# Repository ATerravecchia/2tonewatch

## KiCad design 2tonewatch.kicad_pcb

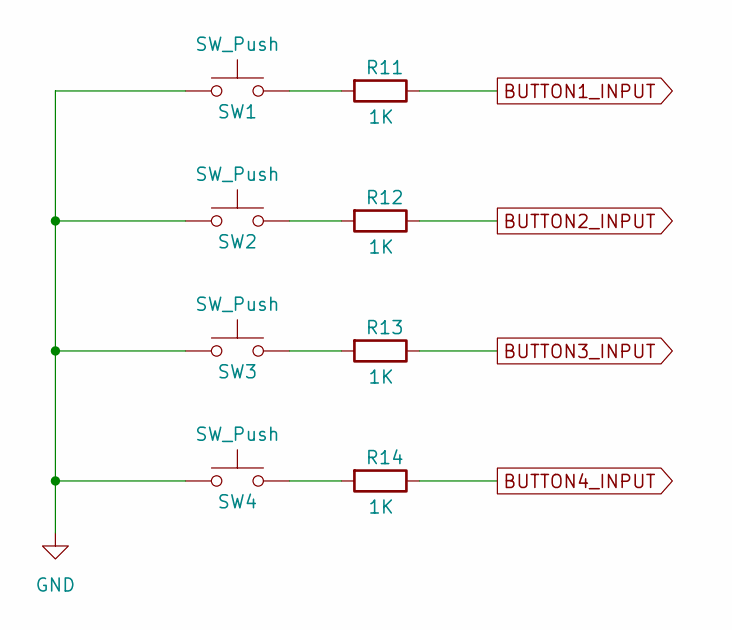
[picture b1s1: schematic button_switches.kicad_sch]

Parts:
R11, R12, R13, R14: 1K; R_0402_1005Metric
SW1, SW2, SW3, SW4: SW_Push; SW_SPST_B3U-3000P; MPN B3U-3000P

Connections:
BUTTON1_INPUT: R11.1; also elsewhere on the board
BUTTON2_INPUT: R12.1; also elsewhere on the board
BUTTON3_INPUT: R13.1; also elsewhere on the board
BUTTON4_INPUT: R14.1; also elsewhere on the board
GND: SW1.1, SW2.1, SW3.1, SW4.1; also elsewhere on the board
unnamed: R11.2, SW1.2
unnamed: R12.2, SW2.2
unnamed: R13.2, SW3.2
unnamed: R14.2, SW4.2

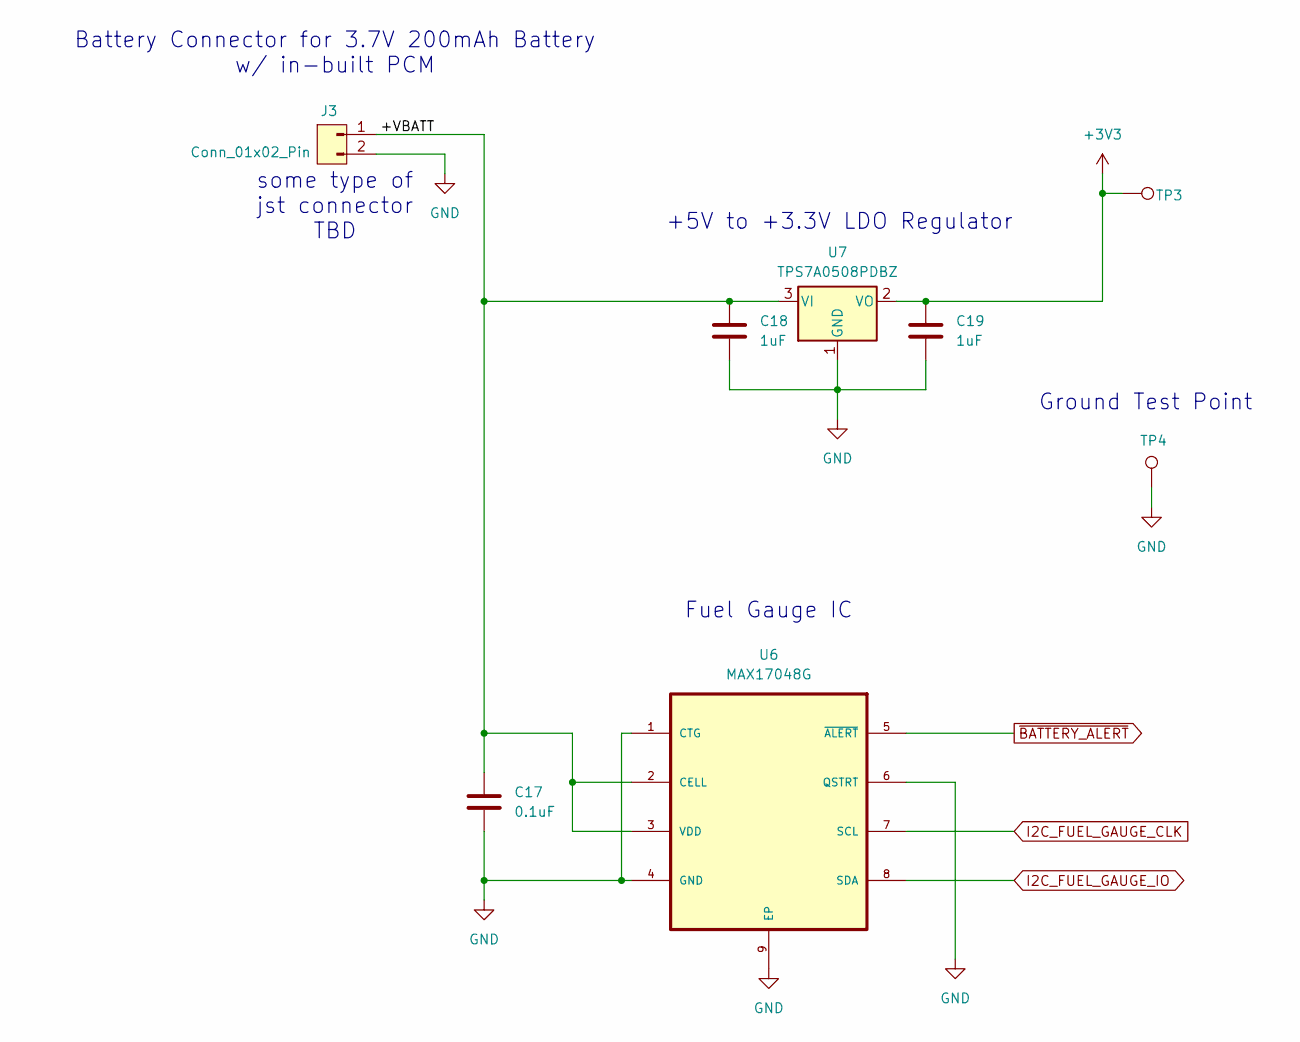
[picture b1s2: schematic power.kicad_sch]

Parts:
C17: 0.1uF; C_0402_1005Metric
C18, C19: 1uF; C_0402_1005Metric
J3: Conn_01x02_Pin; JST_PH_B2B-PH-K_1x02_P2.00mm_Vertical
TP3, TP4: TestPoint_Pad_D1.0mm
U6: MAX17048G; TDFN-8-1EP_2x2mm_P0.5mm_EP0.8x1.2mm
U7: TPS7A0508PDBZ; SOT-23

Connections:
+3V3: C19.1, TP3.1, U7.2 (VO); also elsewhere on the board
/Power/+VBATT: C17.1, C18.1, J3.1, U6.2 (CELL), U6.3 (VDD), U7.3 (VI)
GND: C17.2, C18.2, C19.2, J3.2, TP4.1, U6.1 (CTG), U6.4 (GND), U6.6 (QSTRT), U6.9 (EP), U7.1 (GND); also elsewhere on the board
I2C_FUEL_GAUGE_CLK: U6.7 (SCL); also elsewhere on the board
I2C_FUEL_GAUGE_IO: U6.8 (SDA); also elsewhere on the board
~BATTERY_ALERT: U6.5 (~ALERT); also elsewhere on the board

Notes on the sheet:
Fuel Gauge IC
Ground Test Point
Battery Connector for 3.7V 200mAh Battery w/ in-built PCM
some type of jst connector TBD
+5V to +3.3V LDO Regulator

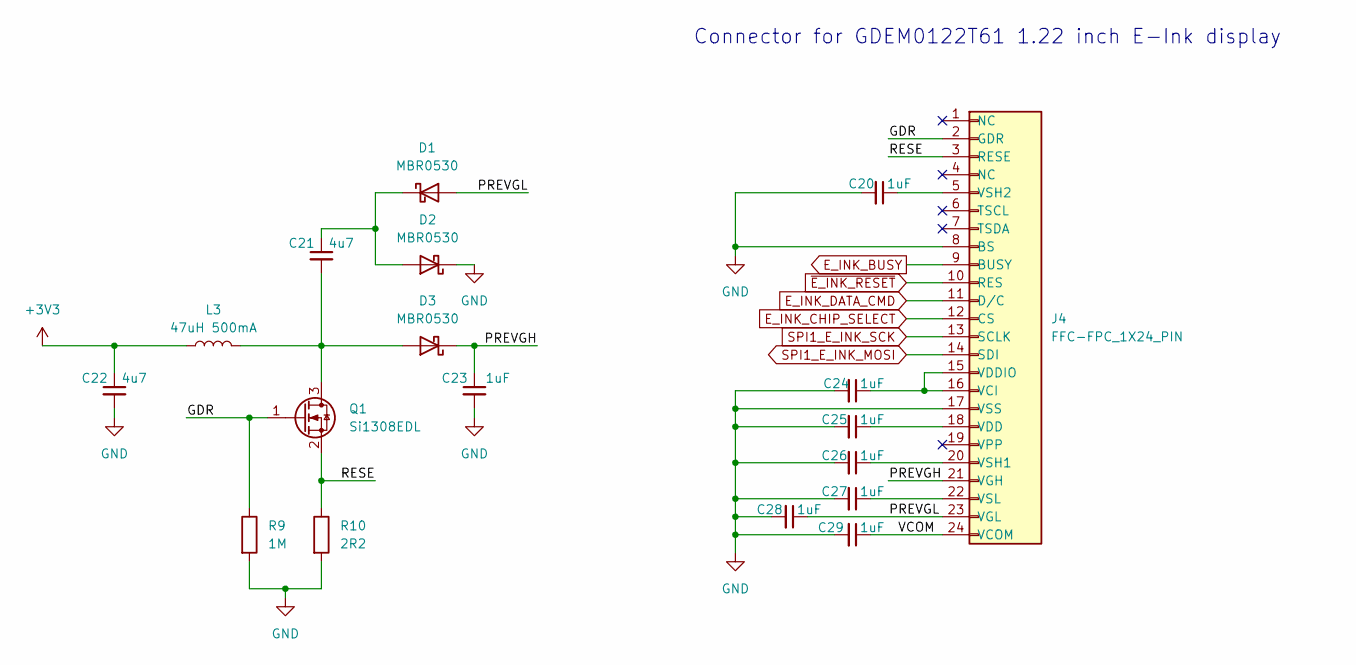
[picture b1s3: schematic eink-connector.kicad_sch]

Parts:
C20, C23, C24, C25, C26, C27, C28, C29: 1uF; C_0603_1608Metric
C21, C22: 4u7; C_0603_1608Metric
D1, D2, D3: MBR0530; D_SOD-123
J4: FFC-FPC_1X24_PIN; Amphenol_F32Q-1A7x1-11024_1x24-1MP_P0.5mm_Horizontal
L3: 47uH 500mA; L_1210_3225Metric; MPN ADL3225V-470MT-TL000
Q1: Si1308EDL; SOT-323_SC-70
R9: 1M; R_0603_1608Metric
R10: 2R2; R_0603_1608Metric

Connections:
+3V3: C22.1, L3.1; also elsewhere on the board
/eink-connector/GDR: J4.2 (GDR), Q1.1 (G), R9.1
/eink-connector/PREVGH: C23.1, D3.1 (K), J4.21 (VGH)
/eink-connector/PREVGL: C28.1, D1.2 (A), J4.23 (VGL)
/eink-connector/RESE: J4.3 (RESE), Q1.2 (S), R10.1
/eink-connector/VCOM: C29.1, J4.24 (VCOM)
E_INK_BUSY: J4.9 (BUSY); also elsewhere on the board
E_INK_CHIP_SELECT: J4.12 (CS); also elsewhere on the board
E_INK_DATA_CMD: J4.11 (D/C); also elsewhere on the board
GND: C20.2, C22.2, C23.2, C24.2, C25.2, C26.2, C27.2, C28.2, C29.2, D2.1 (K), J4.8 (BS), J4.17 (VSS), R9.2, R10.2; also elsewhere on the board
unnamed: C21.1, D1.1 (K), D2.2 (A)
unnamed: C21.2, D3.2 (A), L3.2, Q1.3 (D)
unnamed: C24.1, J4.15 (VDDIO), J4.16 (VCI)
unnamed: C25.1, J4.18 (VDD)
unnamed: C26.1, J4.20 (VSH1)
unnamed: C20.1, J4.5 (VSH2)
unnamed: C27.1, J4.22 (VSL)
SPI1_E_INK_MOSI: J4.14 (SDI); also elsewhere on the board
SPI1_E_INK_SCK: J4.13 (SCLK); also elsewhere on the board
~E_INK_RESET: J4.10 (RES); also elsewhere on the board

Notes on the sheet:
Connector for GDEM0122T61 1.22 inch E-Ink display

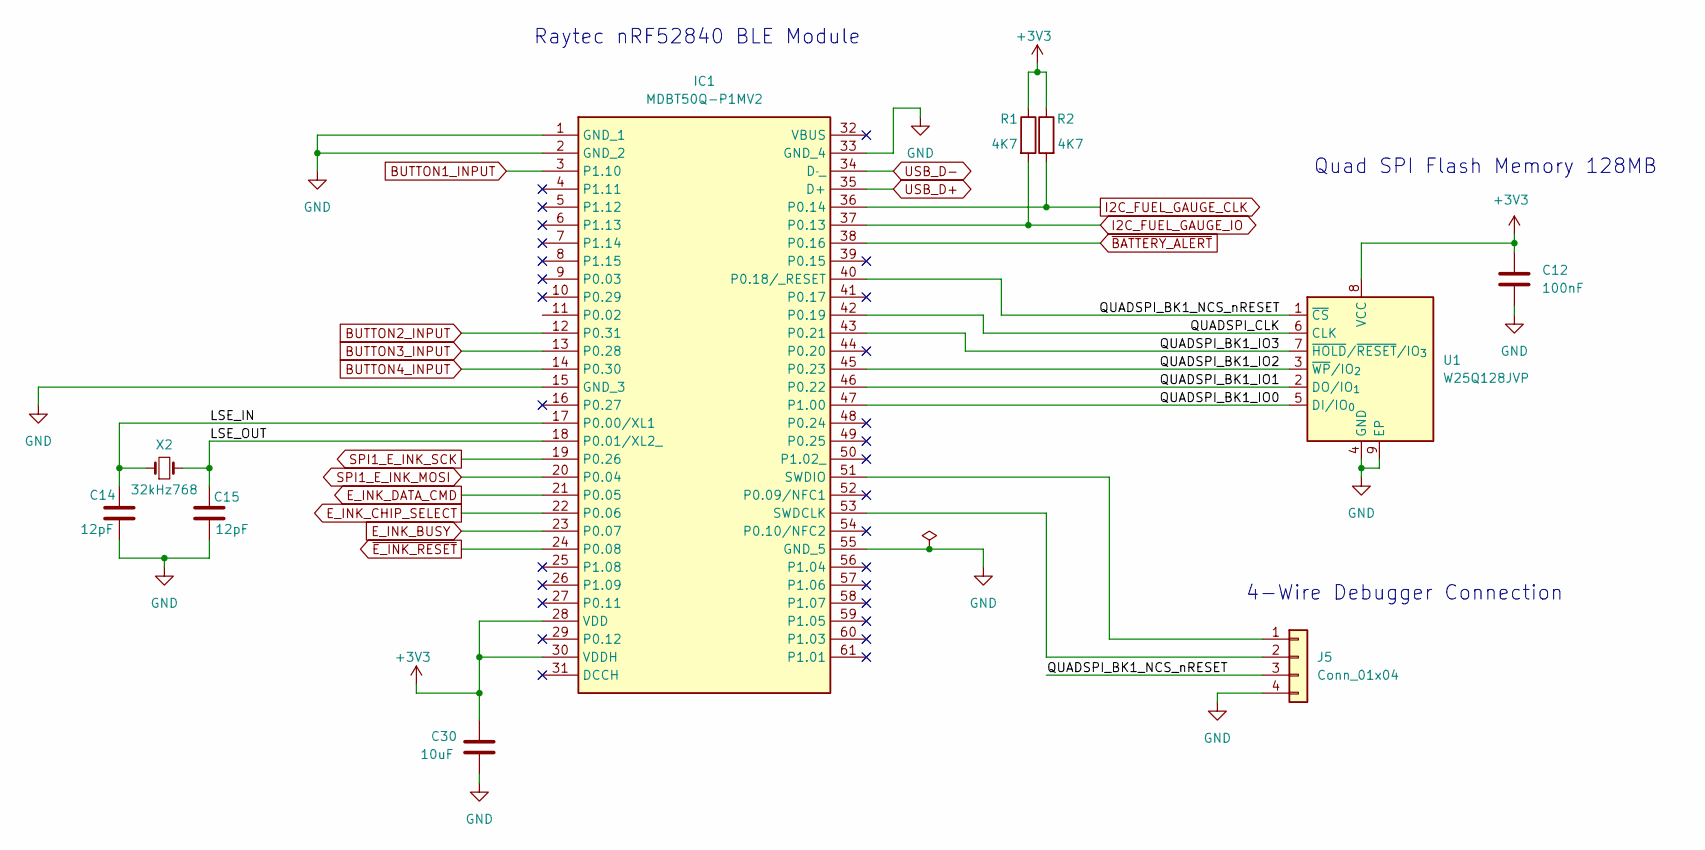
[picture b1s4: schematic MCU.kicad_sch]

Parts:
C12: 100nF; C_0402_1005Metric
C14, C15: 12pF; C_0402_1005Metric
C30: 10uF; C_0603_1608Metric
IC1: MDBT50Q-P1MV2; MDBT50QP1MV2; Manufacturer_Part_Number MDBT50Q-P1MV2
J5: Conn_01x04; PinHeader_1x04_P2.54mm_Vertical
R1, R2: 4K7; R_0402_1005Metric
U1: W25Q128JVP; WSON-8-1EP_6x5mm_P1.27mm_EP3.4x4.3mm
X2: 32kHz768; Crystal_SMD_2012-2Pin_2.0x1.2mm; MPN NX2012_32K768

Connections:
+3V3: C12.1, C30.1, IC1.28 (VDD), IC1.30 (VDDH), R1.1, R2.1, U1.8 (VCC); also elsewhere on the board
/MCU/LSE_IN: C14.1, IC1.17 (P0.00/XL1), X2.1
/MCU/LSE_OUT: C15.1, IC1.18 (P0.01/XL2_), X2.2
/MCU/QUADSPI_BK1_IO0: IC1.47 (P1.00), U1.5 (DI/IO_{0})
/MCU/QUADSPI_BK1_IO1: IC1.46 (P0.22), U1.2 (DO/IO_{1})
/MCU/QUADSPI_BK1_IO2: IC1.45 (P0.23), U1.3 (~WP/IO_{2})
/MCU/QUADSPI_BK1_IO3: IC1.43 (P0.21), U1.7 (~HOLD/~RESET/IO_{3})
/MCU/QUADSPI_BK1_NCS_nRESET: IC1.40 (P0.18/_RESET), J5.3, U1.1 (~CS)
/MCU/QUADSPI_CLK: IC1.42 (P0.19), U1.6 (CLK)
BUTTON1_INPUT: IC1.3 (P1.10); also elsewhere on the board
BUTTON2_INPUT: IC1.12 (P0.31); also elsewhere on the board
BUTTON3_INPUT: IC1.13 (P0.28); also elsewhere on the board
BUTTON4_INPUT: IC1.14 (P0.30); also elsewhere on the board
E_INK_BUSY: IC1.23 (P0.07); also elsewhere on the board
E_INK_CHIP_SELECT: IC1.22 (P0.06); also elsewhere on the board
E_INK_DATA_CMD: IC1.21 (P0.05); also elsewhere on the board
GND: C12.2, C14.2, C15.2, C30.2, IC1.1 (GND_1), IC1.2 (GND_2), IC1.15 (GND_3), IC1.33 (GND_4), IC1.55 (GND_5), J5.4, U1.4 (GND), U1.9 (EP); also elsewhere on the board
I2C_FUEL_GAUGE_CLK: IC1.36 (P0.14), R2.2; also elsewhere on the board
I2C_FUEL_GAUGE_IO: IC1.37 (P0.13), R1.2; also elsewhere on the board
unnamed: IC1.53 (SWDCLK), J5.2
unnamed: IC1.51 (SWDIO), J5.1
SPI1_E_INK_MOSI: IC1.20 (P0.04); also elsewhere on the board
SPI1_E_INK_SCK: IC1.19 (P0.26); also elsewhere on the board
USB_D+: IC1.35 (D+)
USB_D-: IC1.34 (D˗_)
~BATTERY_ALERT: IC1.38 (P0.16); also elsewhere on the board
~E_INK_RESET: IC1.24 (P0.08); also elsewhere on the board

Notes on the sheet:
Quad SPI Flash Memory 128MB
4-Wire Debugger Connection
Raytec nRF52840 BLE Module

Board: 4 copper layers, 44 parts (0 on the bottom side), 42 nets, no tracks yet.

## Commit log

2026-03-03 Initial commit: KiCAD PCB project
2026-03-03 added eink conn page
2026-03-03 eink-> mcu connections
2026-03-04 added decoupling caps on mcu
2026-03-04 generated pdf
2026-03-04 added externals crystal oscillators
2026-03-05 rf and debugger added
2026-03-06 cleaned up rf & connected boot0
2026-03-06 Added external flash ic & 4 push buttons
2026-03-06 updated pdf
2026-03-08 cleaned up some net labels for ERC
2026-03-08 Cleaned up local vs. global net labels
2026-03-09 ERC Check fixes
2026-03-11 Added test points and other cleanup
2026-03-12 changed fram for ic flash memory
2026-03-16 Choose footprints for all parts
2026-03-17 Added layout rules and constraints
2026-04-01 Changed from stm32wb -> nRF52 module
2026-04-01 update netlabel colors
2026-04-13 Layout progress
